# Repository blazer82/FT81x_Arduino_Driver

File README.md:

# FT81x Arduino Driver

[![build-badge]](https://github.com/blazer82/FT81x_Arduino_Driver/actions?workflow=build)
[![docs-badge]](https://github.com/blazer82/FT81x_Arduino_Driver/actions?workflow=docs)

High quality display module for many Arduino project ideas!

## Hardware

Schematics, KiCad files and Gerber files can be found inside the [hardware folder](extras/hardware) in this repository.

The board is compatible with this [display](https://www.buydisplay.com/4-inch-tft-lcd-display-480x480-pixel-with-mipi-interface-for-iot-devices).

The complete hardware is [available for sale on Tindie](https://www.tindie.com/products/prodbld/40-inch-ft81x-tft-lcd-display-module-for-arduino/).

## Highlights

- 4 inch 480x480 pixel TFT display
- up to 24 bit color support
- 19 built-in fonts
- built-in widgets (e.g. buttons, gauges, clock)
- hardware support for JPEG and PNG
- built-in sound effects (audio circuitry required)
- bitmap support with 1 MByte graphics RAM
- open source Arduino library with many example sketches
- compatible with 3.3V and 5V logic levels

## Supported Boards

The hardware and software has been tested with the following boards:

- :heavy_check_mark: Arduino Uno (ATmega328P)
- :heavy_check_mark: Arduino Nano (ATmega328)
- :heavy_check_mark: Arduino Nano Every (ATMega4809)
- :heavy_check_mark: Arduino Due (AT91SAM3X8E)
- :heavy_check_mark: NodeMCU-32S (ESP32)
- :heavy_check_mark: Teensy 4.0 (ARM Cortex M7)

If your board is missing and has full Arduino support chances are that it's fully supported by this library, too.

If you have tested additional boards (successfully or unsuccessfully) feel free to contact me or open an issue.

## Features

| | | |
|-|-|-|
|[x] Line|[x] Circle|[x] Rectangle|
|[x] Gradient|[x] Text|[x] Bitmap images|
|[x] Animated spinner|[x] Sound effects|[x] Buttons|
|[x] Analog clock|[x] Gauge|[x] Line strip|
|[x] JPEG support|[x] PNG support|[x] Scrollbar|
|[x] Audio playback|[x] Progress bar|[ ] Custom fonts|
|[ ] Dial|[ ] Toggle|[ ] Video playback|
|[ ] Keys|||

## Usage

```c++
#include "FT81x.h"

FT81x ft81x = FT81x(10, 9, 8);

void setup() {
    SPI.begin();
    ft81x.begin();

    ft81x.beginDisplayList();
    ft81x.clear(FT81x_COLOR_RGB(0, 0, 0));
    ft81x.drawText(240, 200, 31, FT81x_COLOR_RGB(255, 255, 255), FT81x_OPT_CENTER, "Hello World\0");
    ft81x.swapScreen();
}
```

For more information see the numerous [example sketches](examples) as well as the [API Documentation](https://blazer82.github.io/FT81x_Arduino_Driver/api/class_f_t81x.html).

## Getting Started

For more information on how to get started with the display driver board, please refer to the [Getting Started Guide](https://blazer82.github.io/FT81x_Arduino_Driver).

## License Summary

### Software

MIT License

### Hardware

The hardware is licensed under [CERN-OHL-S v2](https://cern.ch/cern-ohl).

[![oshwa-mark]](https://certification.oshwa.org/de000089.html)

[build-badge]: https://github.com/blazer82/FT81x_Arduino_Driver/workflows/build/badge.svg
[docs-badge]: https://github.com/blazer82/FT81x_Arduino_Driver/workflows/docs/badge.svg
[oshwa-mark]: https://raw.githubusercontent.com/blazer82/FT81x_Arduino_Driver/master/extras/assets/OSHW_mark_DE000089_150.png

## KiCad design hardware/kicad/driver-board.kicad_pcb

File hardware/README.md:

# FT81x Arduino Driver Hardware

## Schematics

### Connectors

### Power

### Level Shifter

### SDI Buffer

### FT81x

### Display

### Testpoints

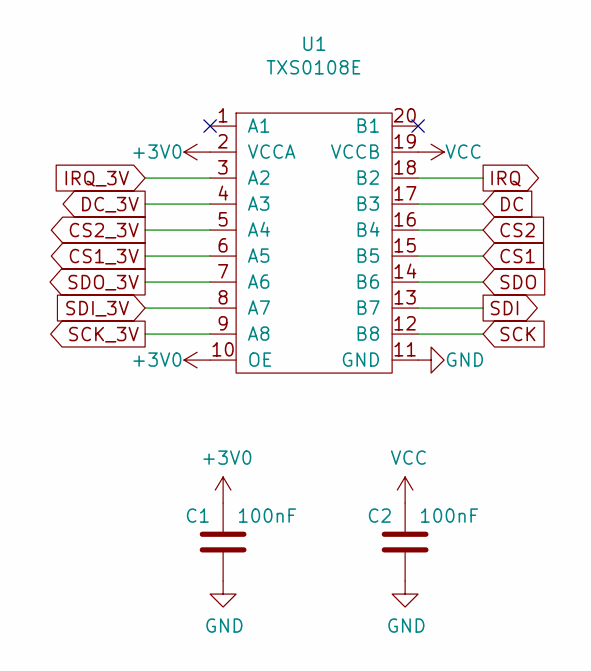
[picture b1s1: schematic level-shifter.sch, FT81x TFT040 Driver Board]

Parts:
C1, C2: 100nF; C_0603_1608Metric; Mfg Part # CC0603KPX7R7BB104; LCSC C14663
U1: TXS0108E; TSSOP-20_4.4x6.5mm_P0.65mm; Mfg Part # TXS0108EPWR; LCSC C17206

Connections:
+3V0: C1.1, U1.2 (VCCA), U1.10 (OE); also elsewhere on the board
CS1: U1.15 (B5); also elsewhere on the board
CS1_3V: U1.6 (A5); also elsewhere on the board
CS2: U1.16 (B4); also elsewhere on the board
CS2_3V: U1.5 (A4); also elsewhere on the board
DC: U1.17 (B3); also elsewhere on the board
DC_3V: U1.4 (A3); also elsewhere on the board
GND: C1.2, C2.2, U1.11 (GND); also elsewhere on the board
IRQ: U1.18 (B2); also elsewhere on the board
IRQ_3V: U1.3 (A2); also elsewhere on the board
SCK: U1.12 (B8); also elsewhere on the board
SCK_3V: U1.9 (A8); also elsewhere on the board
SDI: U1.13 (B7); also elsewhere on the board
SDI_3V: U1.8 (A7); also elsewhere on the board
SDO: U1.14 (B6); also elsewhere on the board
SDO_3V: U1.7 (A6); also elsewhere on the board
VCC: C2.1, U1.19 (VCCB); also elsewhere on the board

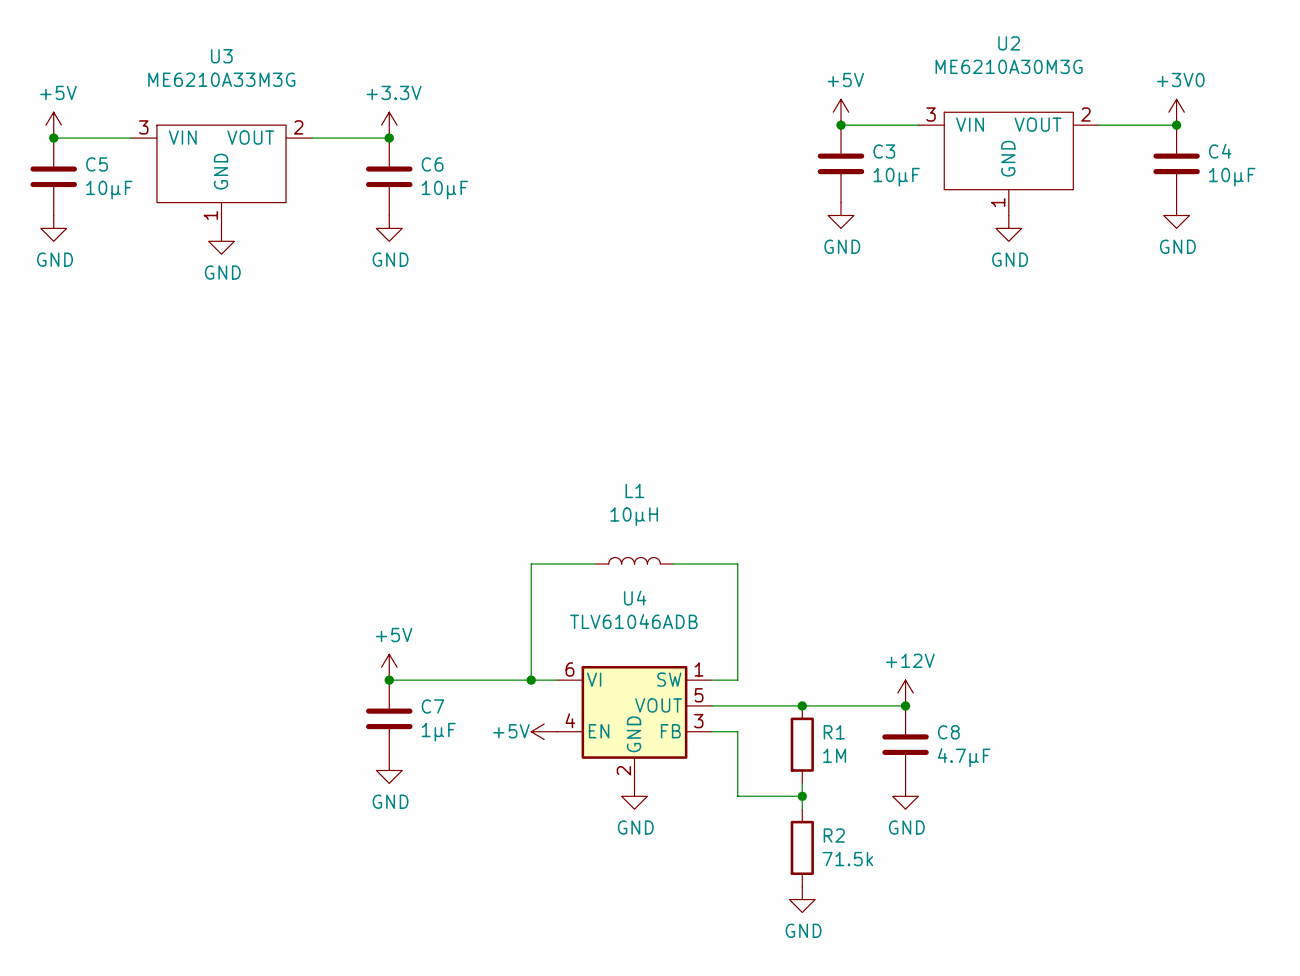
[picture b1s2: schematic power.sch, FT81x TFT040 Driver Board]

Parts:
C3, C4, C5, C6: 10µF; C_0603_1608Metric; Mfg Part # 0603ZD106KAT2A; LCSC C19702
C7: 1µF; C_0603_1608Metric; Mfg Part # CL10A105KP8NNNC; LCSC C15849
C8: 4.7µF; C_0603_1608Metric; Mfg Part # CL10A475KQ8NNNC; LCSC C19666
L1: 10µH; L_0603_1608Metric; Mfg Part # AIML-0603-100K-T; LCSC C1035
R1: 1M; R_0603_1608Metric; Mfg Part # RC0603FR-071ML; LCSC C22935
R2: 71.5k; R_0603_1608Metric; Mfg Part # RC0603FR-0771K5L; LCSC C23103
U2: ME6210A30M3G; SOT-23; Mfg Part # AP2125N-3.0TRG1; LCSC C116985
U3: ME6210A33M3G; SOT-23; Mfg Part # AP2125N-3.3TRG1; LCSC C236680
U4: TLV61046ADB; SOT-23-6; Mfg Part # TLV61046ADBVR; LCSC C464815

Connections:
+3V0: C4.1, U2.2 (VOUT); also elsewhere on the board
+3V3: C6.1, U3.2 (VOUT); also elsewhere on the board
+5V: C3.1, C5.1, C7.1, L1.1, U2.3 (VIN), U3.3 (VIN), U4.4 (EN), U4.6 (VI); also elsewhere on the board
+12V: C8.1, R1.1, U4.5 (VOUT); also elsewhere on the board
GND: C3.2, C4.2, C5.2, C6.2, C7.2, C8.2, R2.2, U2.1 (GND), U3.1 (GND), U4.2 (GND); also elsewhere on the board
unnamed: L1.2, U4.1 (SW)
unnamed: R1.2, R2.1, U4.3 (FB)

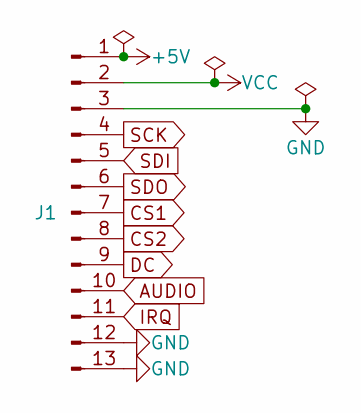
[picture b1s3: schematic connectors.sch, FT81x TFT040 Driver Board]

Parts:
J1: Conn_01x13_Male; PinHeader_1x13_P2.54mm_Vertical

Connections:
+5V: J1.1; also elsewhere on the board
AUDIO: J1.10; also elsewhere on the board
CS1: J1.7; also elsewhere on the board
CS2: J1.8; also elsewhere on the board
DC: J1.9; also elsewhere on the board
GND: J1.3, J1.12, J1.13; also elsewhere on the board
IRQ: J1.11; also elsewhere on the board
SCK: J1.4; also elsewhere on the board
SDI: J1.5; also elsewhere on the board
SDO: J1.6; also elsewhere on the board
VCC: J1.2; also elsewhere on the board

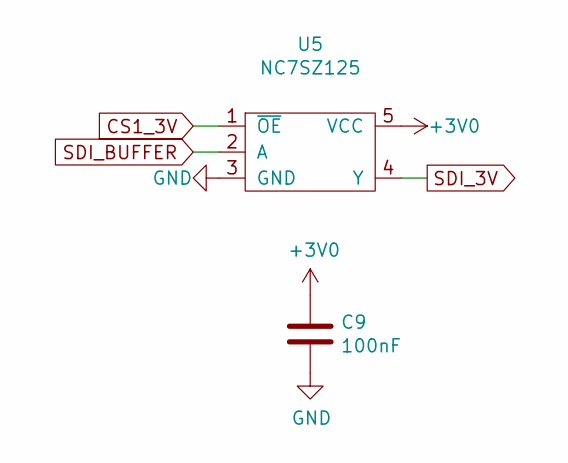
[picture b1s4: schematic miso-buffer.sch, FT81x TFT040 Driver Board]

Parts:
C9: 100nF; C_0603_1608Metric; Mfg Part # CC0603KPX7R7BB104; LCSC C14663
U5: NC7SZ125; SOT-23-5; Mfg Part # NC7SZ125M5X; LCSC C7420

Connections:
+3V0: C9.1, U5.5 (VCC); also elsewhere on the board
CS1_3V: U5.1 (~OE); also elsewhere on the board
GND: C9.2, U5.3 (GND); also elsewhere on the board
SDI_3V: U5.4 (Y); also elsewhere on the board
SDI_BUFFER: U5.2 (A); also elsewhere on the board

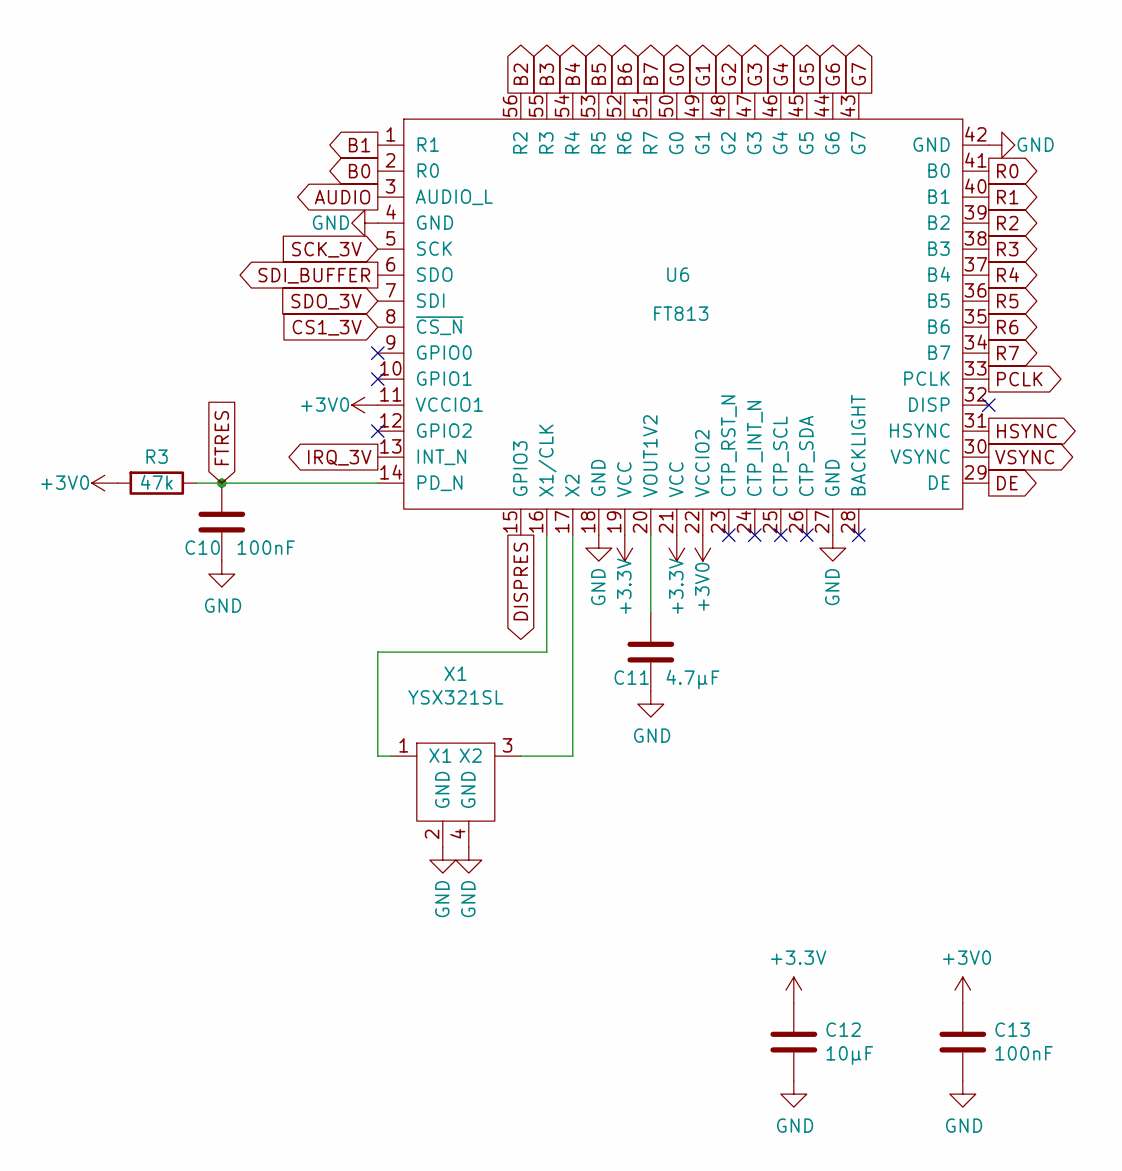
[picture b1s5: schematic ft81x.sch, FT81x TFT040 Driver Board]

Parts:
C10, C13: 100nF; C_0603_1608Metric; Mfg Part # CC0603KPX7R7BB104; LCSC C14663
C11: 4.7µF; C_0603_1608Metric; Mfg Part # CL10A475KQ8NNNC; LCSC C19666
C12: 10µF; C_0603_1608Metric; Mfg Part # 0603ZD106KAT2A; LCSC C19702
R3: 47k; R_0603_1608Metric; Mfg Part # RC0603JR-0747KL; LCSC C25819
U6: FT813; QFN-56-1EP_8x8mm_P0.5mm_EP5.6x5.6mm; Mfg Part # FT812Q-T
X1: YSX321SL; Crystal_SMD_3225-4Pin_3.2x2.5mm; Mfg Part # RH100-12.000-12-1010-EXT-TR; LCSC C9002

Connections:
+3V0: C13.1, R3.2, U6.11 (VCCIO1), U6.22 (VCCIO2); also elsewhere on the board
+3V3: C12.1, U6.19 (VCC), U6.21 (VCC); also elsewhere on the board
AUDIO: U6.3 (AUDIO_L); also elsewhere on the board
B0: U6.2 (R0); also elsewhere on the board
B1: U6.1 (R1); also elsewhere on the board
B2: U6.56 (R2); also elsewhere on the board
B3: U6.55 (R3); also elsewhere on the board
B4: U6.54 (R4); also elsewhere on the board
B5: U6.53 (R5); also elsewhere on the board
B6: U6.52 (R6); also elsewhere on the board
B7: U6.51 (R7); also elsewhere on the board
CS1_3V: U6.8 (~CS_N); also elsewhere on the board
DE: U6.29 (DE); also elsewhere on the board
DISPRES: U6.15 (GPIO3); also elsewhere on the board
FTRES: C10.1, R3.1, U6.14 (PD_N); also elsewhere on the board
G0: U6.50 (G0); also elsewhere on the board
G1: U6.49 (G1); also elsewhere on the board
G2: U6.48 (G2); also elsewhere on the board
G3: U6.47 (G3); also elsewhere on the board
G4: U6.46 (G4); also elsewhere on the board
G5: U6.45 (G5); also elsewhere on the board
G6: U6.44 (G6); also elsewhere on the board
G7: U6.43 (G7); also elsewhere on the board
GND: C10.2, C11.2, C12.2, C13.2, U6.4 (GND), U6.18 (GND), U6.27 (GND), U6.42 (GND), U6.57 (GND), X1.2 (GND), X1.4 (GND); also elsewhere on the board
HSYNC: U6.31 (HSYNC); also elsewhere on the board
IRQ_3V: U6.13 (INT_N); also elsewhere on the board
unnamed: C11.1, U6.20 (VOUT1V2)
unnamed: U6.16 (X1/CLK), X1.1 (X1)
unnamed: U6.17 (X2), X1.3 (X2)
PCLK: U6.33 (PCLK); also elsewhere on the board
R0: U6.41 (B0); also elsewhere on the board
R1: U6.40 (B1); also elsewhere on the board
R2: U6.39 (B2); also elsewhere on the board
R3: U6.38 (B3); also elsewhere on the board
R4: U6.37 (B4); also elsewhere on the board
R5: U6.36 (B5); also elsewhere on the board
R6: U6.35 (B6); also elsewhere on the board
R7: U6.34 (B7); also elsewhere on the board
SCK_3V: U6.5 (SCK); also elsewhere on the board
SDI_BUFFER: U6.6 (SDO); also elsewhere on the board
SDO_3V: U6.7 (SDI); also elsewhere on the board
VSYNC: U6.30 (VSYNC); also elsewhere on the board

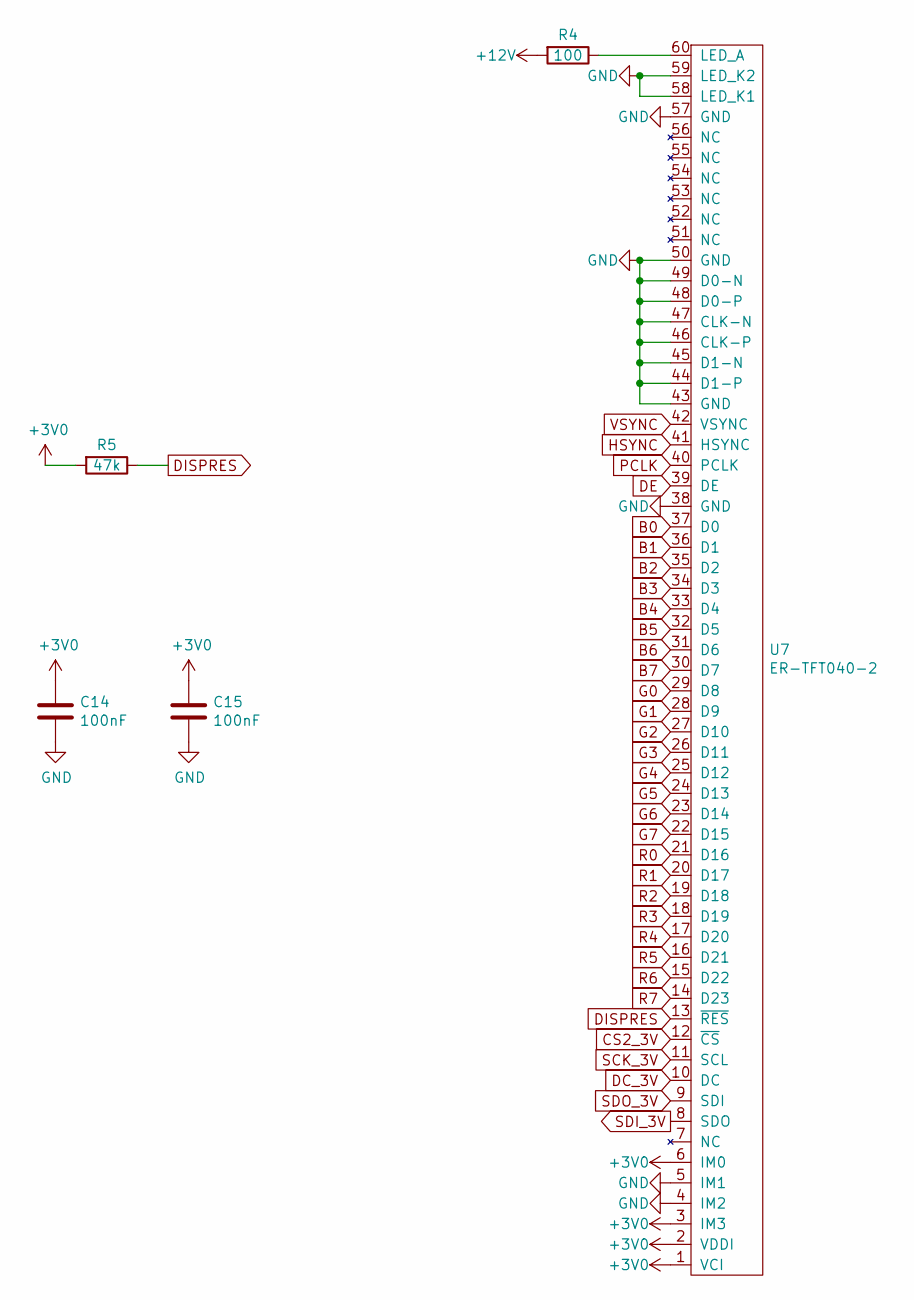
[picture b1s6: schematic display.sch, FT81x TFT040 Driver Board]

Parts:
C14, C15: 100nF; C_0603_1608Metric; Mfg Part # CC0603KPX7R7BB104; LCSC C14663
R4: 100; R_0603_1608Metric; Mfg Part # RC0603FR-07100RL; LCSC C22775
R5: 47k; R_0603_1608Metric; Mfg Part # RC0603JR-0747KL; LCSC C25819
U7: ER-TFT040-2; HRS_FH28-60S-0.5SH(05); Mfg Part # FH28-60S-0.5SH(05)

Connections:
+3V0: C14.1, C15.1, R5.2, U7.1 (VCI), U7.2 (VDDI), U7.3 (IM3), U7.6 (IM0); also elsewhere on the board
+12V: R4.2; also elsewhere on the board
B0: U7.37 (D0); also elsewhere on the board
B1: U7.36 (D1); also elsewhere on the board
B2: U7.35 (D2); also elsewhere on the board
B3: U7.34 (D3); also elsewhere on the board
B4: U7.33 (D4); also elsewhere on the board
B5: U7.32 (D5); also elsewhere on the board
B6: U7.31 (D6); also elsewhere on the board
B7: U7.30 (D7); also elsewhere on the board
CS2_3V: U7.12 (~CS); also elsewhere on the board
DC_3V: U7.10 (DC); also elsewhere on the board
DE: U7.39 (DE); also elsewhere on the board
DISPRES: R5.1, U7.13 (~RES); also elsewhere on the board
G0: U7.29 (D8); also elsewhere on the board
G1: U7.28 (D9); also elsewhere on the board
G2: U7.27 (D10); also elsewhere on the board
G3: U7.26 (D11); also elsewhere on the board
G4: U7.25 (D12); also elsewhere on the board
G5: U7.24 (D13); also elsewhere on the board
G6: U7.23 (D14); also elsewhere on the board
G7: U7.22 (D15); also elsewhere on the board
GND: C14.2, C15.2, U7.4 (IM2), U7.5 (IM1), U7.38 (GND), U7.43 (GND), U7.44 (D1-P), U7.45 (D1-N), U7.46 (CLK-P), U7.47 (CLK-N), U7.48 (D0-P), U7.49 (D0-N), U7.50 (GND), U7.57 (GND), U7.58 (LED_K1), U7.59 (LED_K2); also elsewhere on the board
HSYNC: U7.41 (HSYNC); also elsewhere on the board
unnamed: R4.1, U7.60 (LED_A)
PCLK: U7.40 (PCLK); also elsewhere on the board
R0: U7.21 (D16); also elsewhere on the board
R1: U7.20 (D17); also elsewhere on the board
R2: U7.19 (D18); also elsewhere on the board
R3: U7.18 (D19); also elsewhere on the board
R4: U7.17 (D20); also elsewhere on the board
R5: U7.16 (D21); also elsewhere on the board
R6: U7.15 (D22); also elsewhere on the board
R7: U7.14 (D23); also elsewhere on the board
SCK_3V: U7.11 (SCL); also elsewhere on the board
SDI_3V: U7.8 (SDO); also elsewhere on the board
SDO_3V: U7.9 (SDI); also elsewhere on the board
VSYNC: U7.42 (VSYNC); also elsewhere on the board

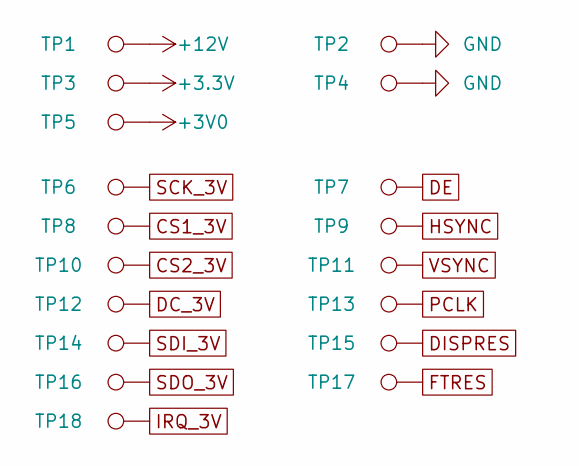
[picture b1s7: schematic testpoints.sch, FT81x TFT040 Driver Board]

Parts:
TP1, TP3, TP5, TP6, TP7, TP8, TP9, TP10, TP11, TP12, TP13, TP14, TP15, TP16, TP17, TP18: TestPoint; TestPoint_Pad_D0.5mm
TP2, TP4: TestPoint; TestPoint_Pad_1.0x1.0mm

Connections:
+3V0: TP5.1; also elsewhere on the board
+3V3: TP3.1; also elsewhere on the board
+12V: TP1.1; also elsewhere on the board
CS1_3V: TP8.1; also elsewhere on the board
CS2_3V: TP10.1; also elsewhere on the board
DC_3V: TP12.1; also elsewhere on the board
DE: TP7.1; also elsewhere on the board
GND: TP2.1, TP4.1; also elsewhere on the board
HSYNC: TP9.1; also elsewhere on the board
PCLK: TP13.1; also elsewhere on the board
SCK_3V: TP6.1; also elsewhere on the board
SDI_3V: TP14.1; also elsewhere on the board
SDO_3V: TP16.1; also elsewhere on the board
VSYNC: TP11.1; also elsewhere on the board

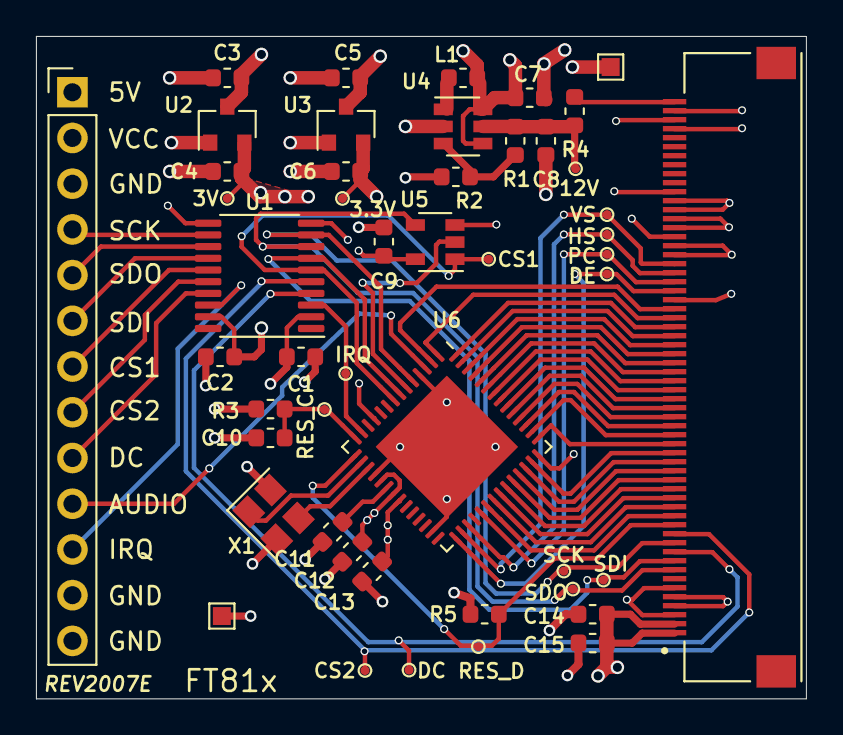
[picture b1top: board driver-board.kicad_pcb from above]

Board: 4 copper layers, 42.8 x 36.8 mm, 49 parts (1 on the bottom side), 58 nets.

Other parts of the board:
IRQ: TestPoint; TestPoint_Pad_D0.5mm
OSHW Logo: OSHW-Logo2_9.8x8mm_SilkScreen
RES_C: TestPoint; TestPoint_Pad_D0.5mm
RES_D: TestPoint; TestPoint_Pad_D0.5mm

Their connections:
DISPRES: RES_D.1; also elsewhere on the board
FTRES: RES_C.1; also elsewhere on the board
IRQ_3V: IRQ.1; also elsewhere on the board

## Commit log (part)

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2020-04-03 FT81x driver on work
2020-04-04 Fixed byte order
2020-04-05 Added ST7701 initialization
2020-04-05 Display lists on work
2020-04-25 We've got a green screen!
2020-04-26 Broken circles and broken frame swap
2020-04-27 Modified test code
2020-04-27 Updated ic config
2020-04-27 Stuff on work
2020-04-29 on work
2020-04-30 Refactored display cmd interface
2020-04-30 Added init code copied from linux driver for display
2020-05-02 On work yet still not working
2020-05-04 Copied command sequence from google groups
2020-05-07 Got the correct init sequence for the display
2020-05-07 Some clean up
2020-05-07 Added cpplint
2020-05-08 Added license file headers
2020-05-08 Added license file
2020-05-08 Added readme
2020-05-09 Wait for circular buffer to catch up for new display lists
2020-05-10 Implemented basic bitmap example
2020-05-10 Fixed issue with bitmap display
2020-05-10 Some clean-up
2020-05-14 Updated for use with gb teensy
2020-05-23 Teensy DMA on work
2020-05-24 Working non-blocking GRAM transfer example
2020-05-25 Added clang-format config
2020-05-25 Added support for larger gram transfers
2020-05-30 Added nop to empty loops
2020-05-30 Added license to dma spi lib
2020-05-30 Adopted the arduino style API
2020-05-30 Integrated dma with non-dma implementation
2020-05-30 Fixed minor issues
2020-05-30 Added drawText method
2020-05-30 Added option defines
2020-05-30 Added spinner command
2020-05-31 Removed unused dl method
2020-05-31 Improved sending of cmd sequences
2020-05-31 Some DMA performance improvements
2020-06-01 Potential performance improvement for GRAM transfers
2020-06-01 Clarified parameter naming for text
2020-06-13 Adaptation to the new board and fixes
2020-06-13 Minor improvement to spi communictation
2020-06-14 Prevent unnecessary toggle of dc pin
2020-06-20 Fix query display function
2020-07-03 Add work-in-progress kicad hardware files
2020-07-05 Add display schematics
2020-07-06 Update some symbols
2020-07-06 Add testpoints
2020-07-06 Update board setup
2020-07-06 PCB layout on work
2020-07-06 Update display connector footprint to hand solder
2020-07-07 Add more pin header pins
2020-07-08 Board layout on work
2020-07-08 Adapt new SPI signal names from OSHWA
2020-07-08 Improve and fix pcb and schematic
2020-07-08 Add missing JLCPCB part numbers
2020-07-08 Rename JLCPCB to LCSC and update PCB
2020-07-08 Add drop-in replacement for buffer IC
2020-07-09 Cleanup kicad related files
2020-07-09 Add more st7701 definitions
2020-07-09 Fix return value of read32 function
2020-07-09 Fix shift count overflow for avr platform
2020-07-10 Convert to arduino library structure
2020-07-10 Add doxygen
2020-07-10 Add travis config
2020-07-10 Update travis config
2020-07-10 Remove clang-format from travis
2020-07-10 Remove custom doxyfile
2020-07-10 Update inline documentation for ft81x
2020-07-10 Deploy code docs to GitHub Pages Travis build: 6
    Commit: f4cb5bc9c08ad7ae7150c813bd9186315266e9da
2020-07-10 Add link to api doc to readme
2020-07-10 Reorganize hardware files
2020-07-10 Reorganize hardware assets
2020-07-10 Update image descriptions for schematics
2020-07-10 Update main readme
2020-07-10 Add license summary to main readme
2020-07-11 Add hello world example
2020-07-11 Switch from travis to github workflows
2020-07-11 Simple CI test build
2020-07-11 Dynamically build example sketches
2020-07-11 Add more colorful build output
2020-07-11 Add github CI build badge to readme
2020-07-11 Add esp8266 node mcu platform to build
2020-07-11 Fix build script
2020-07-11 Add esp32 to ci build
2020-07-11 Add Doxyfile
2020-07-11 Deploy code docs to github pages 2
    Commit: 0a110fbb0df99096ecd0230c35b1f5bb7e8bb10a
2020-07-11 Add docs workflow
2020-07-11 Deploy code docs to github pages 4
    Commit: 78429b47ad6d4249d6ca71e0e21dc9ba1a4b4809
2020-07-11 Deploy code docs to github pages 6
    Commit: 7781f5afcc551699f12a787ddb0ce0a1c24c311a
2020-07-11 Deploy code docs to github pages 7
    Commit: 1cf807841fdbe8efb1aa42e10d4c194d1fea5228
2020-07-11 Properly link build badges
2020-07-11 Deploy code docs to github pages 10
    Commit: e410c23e13237a7c317ee313147c0cf1680b0c8f
2020-07-11 Check for master branch when updating docs
2020-07-11 Deploy code docs to github pages 16
    Commit: 258b065a66d5bc2ac2e84bb6e0031d3aede42d26
2020-07-12 Add platformio build to ci
2020-07-12 Fix arduino samd build by properly excluding DmaSpi
2020-07-12 Deploy code docs to github pages 23
    Commit: 65c2b5ed03d01a4ced6e4ad5ba9973df37bd3136
2020-07-12 Add clang-format lint to build
2020-07-12 Deploy code docs to github pages 28
    Commit: 858bf727be649ae0925aee29fc015e18a241dca0
2020-07-13 Remove license file
2020-07-13 Switch to MIT license
2020-07-13 Deploy code docs to github pages 33
    Commit: 9d17dcd735ca5b2910047b7f52ac4c54c4df508d
2020-07-14 Update project name in doxyfile
2020-07-14 Move teensy specific dma code to subfolder
2020-07-14 Deploy code docs to github pages 34
    Commit: 9917be6753f3f250d332c633110ef8c43b0232be
2020-07-15 Adapt globstar matcher
2020-07-15 Move source files to src folder
2020-07-15 Change doxygen input to src
2020-07-16 Carify power IC symbol names
2020-07-16 Add platformio library file
2020-07-17 Adaptions for REV2007D board and dynamic pin initialization
2020-07-17 Deploy code docs to github pages 42
    Commit: a39251de06e3c03090244ab9923625e27ad071c6
2020-07-17 Deploy code docs to github pages 43
    Commit: 0277cfa15e1dcb435ffafb06fdde02d5aec9a3f1
2020-07-17 Update documentation
2020-07-18 Change min drill size to 0.3
2020-07-18 Rework display reset circuit and improve 3v power supply
2020-07-18 Add digikey bom alternative
2020-07-19 Update footprints for machine assembly
2020-07-19 Add OSHW logo
2020-07-19 Update schematics plot
2020-07-19 Clean up board and expose less debug signals
2020-07-19 Update BOM
2020-07-19 Update schematics meta data
2020-07-19 Set origin points in pcb file
2020-07-19 Update display connector footprint properties to SMD
2020-07-19 Add support for sound effects
2020-07-19 Deploy code docs to github pages 53
    Commit: 3b346a19d2df25f99fe0b58423c0054c8c6ac1a5
2020-07-19 Deploy code docs to github pages 54
    Commit: 7a1bb0c44fff1c31188ef6737d660de70c9da0e2
2020-07-19 Implement button draw command
2020-07-19 Deploy code docs to github pages 55
    Commit: 7dbb1c66b25358ad78c0ecded8ae1f8e894797cf
2020-07-20 Add usage example to readme
2020-07-20 Add arduino nano boards to tested boards
2020-07-21 Update inductor in schematics
2020-07-21 Add official Arduino Due support
2020-07-21 Implement analog clock display and improve button function
2020-07-21 Deploy code docs to github pages 59
    Commit: 5c847ff224282f4843308de541ed3fbdcee3d1d9
2020-07-22 Set SPI clock speed based on architecture
2020-07-22 Deploy code docs to github pages 60
    Commit: a03b2a4808a796d98cf4bd131ad5223c7892186c
2020-07-22 Set pixel clock to 20 mhz at 70 fps
2020-07-23 Document successful tests with 5v systems
2020-07-24 Add example sketches for audio, buttons and clock
2020-07-24 Fix platformio build script
2020-07-24 Update audio example
2020-07-25 Add link to example sketech to readme
2020-07-25 Prefix SPI_CLOCK_SPEED
2020-07-25 Deploy code docs to github pages 69
    Commit: 79ba60674a64a23d87ca2a905254b9ff258095f4
2020-07-25 Fix issue with color calculation
2020-07-25 Deploy code docs to github pages 70
    Commit: d75db83ec8e554ef3c13783aa06775f1b4046af8
2020-07-25 Deploy code docs to github pages 71
    Commit: ab15841e80cc48560e3e9725b989a825dd39e6c4
2020-07-25 Implement gauge widget
2020-07-25 Deploy code docs to github pages 73
    Commit: e9c5e09fff8dacdd651e2ed8b47bf76580e5e648
2020-07-25 Implement gradient
2020-07-25 Deploy code docs to github pages 74
    Commit: 5c7c7a5a3cb87a0ff3c68adecfb7c28de3b0979a
2020-07-26 Fix issues with teensy dma
2020-07-27 Add gradient to feature list
2020-07-28 Implement line primitive
2020-07-28 Deploy code docs to github pages 77
    Commit: 78990f15f3c3b638f11973083f5005a65871b5e5
2020-07-30 Add line strip support and advanced tech demo for 3d wireframe
2020-07-30 Deploy code docs to github pages 78
    Commit: 12921ac094a9e40c58b617ff5aedebc958dc34d9
2020-07-30 Update documentation and examples
2020-07-31 Extend 3d tech demo
2020-07-31 Deploy code docs to github pages 82
    Commit: 7b5cdf70d40ecafe29c618fa9d8b6bebe615f19e
2020-07-31 Add apt update to build script
2020-07-31 Add const to example sketch
2020-08-02 Deploy code docs to github pages 85
    Commit: 6c853935dec889505a3794876a05572f44b8b9e4
2020-08-06 Fix issue with display vertical cycle
2020-08-06 Add support for all rom fonts and add text example
2020-08-06 Deploy code docs to github pages 87
    Commit: e07b5f781fc4d6ccc664635d4825592a0993963b
2020-08-11 shrunk board down to two layers
2020-08-11 Cleaned up 2L board a bit, generated gerbers. Ordering from boardhouse
2020-08-12 Remove redundant line
2020-08-14 Deploy code docs to github pages 89
    Commit: 3b7748193bd4d5d89f80e62b0f882b8f5328386f
2020-08-14 Remove reset pin dependency
2020-08-16 Update library property files
2020-08-16 Add license file to teensy dma implementation
2020-08-16 Add teensy30 to platform.io build
2020-08-17 Add image of real hardware
2020-08-20 Update readme and add tindie link
2020-08-20 Work-in-progress DMA support for ESP32
2020-08-21 Output api docs to api folder instead of html
2020-08-21 Deploy code docs to github pages 105
    Commit: d0d13b6c2115638a7f54bd113d0210e819e91507
2020-08-21 New docs initial commit
2020-08-21 Remove .DS_Store files
2020-08-21 Add gitignore
2020-08-21 new docs on work
2020-08-21 Improve performance of 3d tech demo by removing 64 bit maths
2020-08-22 Add getting started guide
2020-08-22 Update readme and add getting started guide
2020-08-22 Add link to github profile
2020-08-22 Update html title
2020-08-26 Fix github link
2020-08-27 Add oshwa mark
2020-08-27 Add output to doxygen script
2020-08-27 Update doxygen download link
2020-09-01 Fix typo
2020-09-01 Deploy code docs to github pages 111
    Commit: 6b4bba7ffc397d2b48c52dc5b6f4266fb84cadeb
2020-09-01 Add audio setup guide
2020-09-01 Update audio breadboard image
2020-09-03 Update audio schematics
2020-09-06 Introduce extras folder according to Arduino library specs
2020-09-06 Update version
2020-09-14 Update installation part of docs
2020-09-17 Add scrollbar support with example sketch
2020-09-17 Add changes to workflow config
2020-09-17 Add scrollbar support with example sketch (#4)
    * Add scrollbar support with example sketch
    * Add changes to workflow config
2020-09-17 Deploy code docs to github pages 119
    Commit: b13ee394de15244352f7af4ddb6e2085e9ac67ad
2020-09-26 Add audio playback and option to avoid progmem for gram data transfers
2020-09-29 Set playback volume with audio volume
2020-09-29 Add audio playback example
2020-09-29 Add audio playback and option to avoid progmem for gram data transfers (#5)
    * Add audio playback and option to avoid progmem for gram data transfers
    * Set playback volume with audio volume
    * Add audio playback example
2020-10-18 Update board to aisler specs
2020-12-20 Add support for progressbar widget
2020-12-20 Update readme and version
2020-12-20 Add support for progressbar widget (#6)
    * Add support for progressbar widget
    * Update readme and version
2020-12-20 Deploy code docs to github pages 126
    Commit: 690fe9fef78f691fbf7279b5567ab24e6f9900e1
2021-01-14 Reformat and update docs
2021-04-17 Update parts bom
2021-09-15 Clean up kicad project
2023-03-28 Added triangles and bitmap overlays
2023-04-04 Clang formatting
2023-04-04 Update example code to adapted drawBitmap signature
2023-04-04 Added support for drawing triangles and image overlays (#12)
    * Added triangles and bitmap overlays
    * Added triangles and bitmap overlays
    * Update src/FT81x.h
    * Clang formatting
    * Update example code to adapted drawBitmap signature
    ---------
2023-04-04 Fix docs workflow
2023-04-04 Deploy code docs to github pages 138
    Commit: cad5b1ab7ced2ef9ae59c2d034b62c412fb428d2
2024-06-12 Fix wrong ARGB1555 constant (Thanks @dinoghi)
2024-06-12 Deploy code docs to github pages 139
    Commit: 26fc40df5e27cc81693015e949f2f877ea08863b

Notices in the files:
hardware/kicad/driver-board.kicad_pcb:
Copyright © Raphael Stäbler
